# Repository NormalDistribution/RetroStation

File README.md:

A retro handheld gamestation based on the Raspberry Pi.

Be sure to check out our product status page:
https://github.com/NormalDistribution/RetroStation/wiki

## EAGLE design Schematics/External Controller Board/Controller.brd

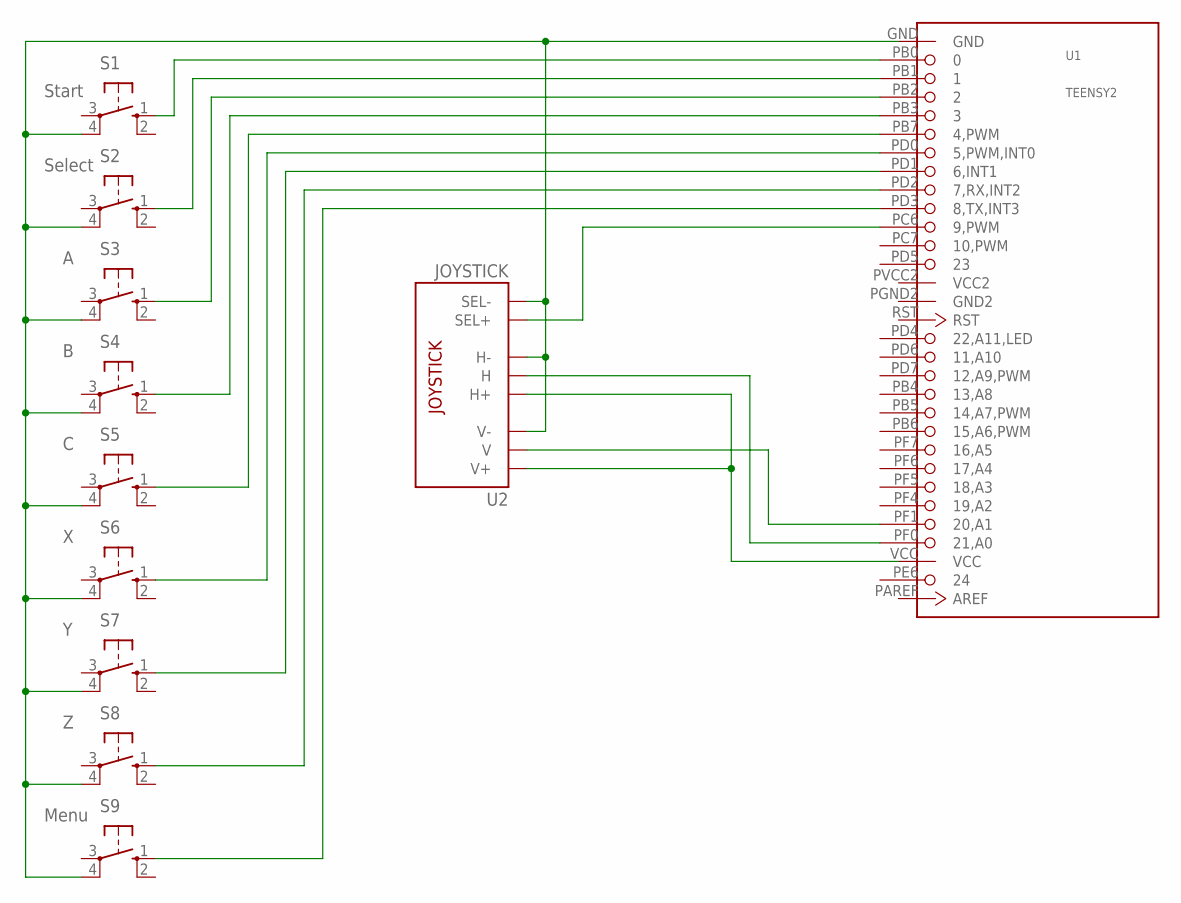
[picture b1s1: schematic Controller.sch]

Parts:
S1, S2, S3, S4, S5, S6, S7, S8, S9: 10-XX; B3F-10XX
U1: TEENSY2
U2: JOYSTICK

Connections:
GND2: U1.PGND2 (GND2)
unnamed: S1.1 (S), U1.PB0 (0)
unnamed: S2.1 (S), U1.PB1 (1)
unnamed: S3.1 (S), U1.PB2 (2)
unnamed: S4.1 (S), U1.PB3 (3)
unnamed: S5.1 (S), U1.PB7 (4,PWM)
unnamed: S6.1 (S), U1.PD0 (5,PWM,INT0)
unnamed: S7.1 (S), U1.PD1 (6,INT1)
unnamed: S8.1 (S), U1.PD2 (7,RX,INT2)
unnamed: U1.PC6 (9,PWM), U2.B1A (SEL+)
unnamed: U1.VCC, U2.H1 (H+), U2.V1 (V+)
unnamed: U1.PF0 (21,A0), U2.H2 (H)
unnamed: S9.1 (S), U1.PD3 (8,TX,INT3)
unnamed: S1.4 (P1), S2.4 (P1), S3.4 (P1), S4.4 (P1), S5.4 (P1), S6.4 (P1), S7.4 (P1), S8.4 (P1), S9.4 (P1), U1.GND, U2.B2A (SEL-), U2.H3 (H-), U2.V3 (V-)
unnamed: U1.PF1 (20,A1), U2.V2 (V)
VCC2: U1.PVCC2 (VCC2)

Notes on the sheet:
Start
Select
Menu

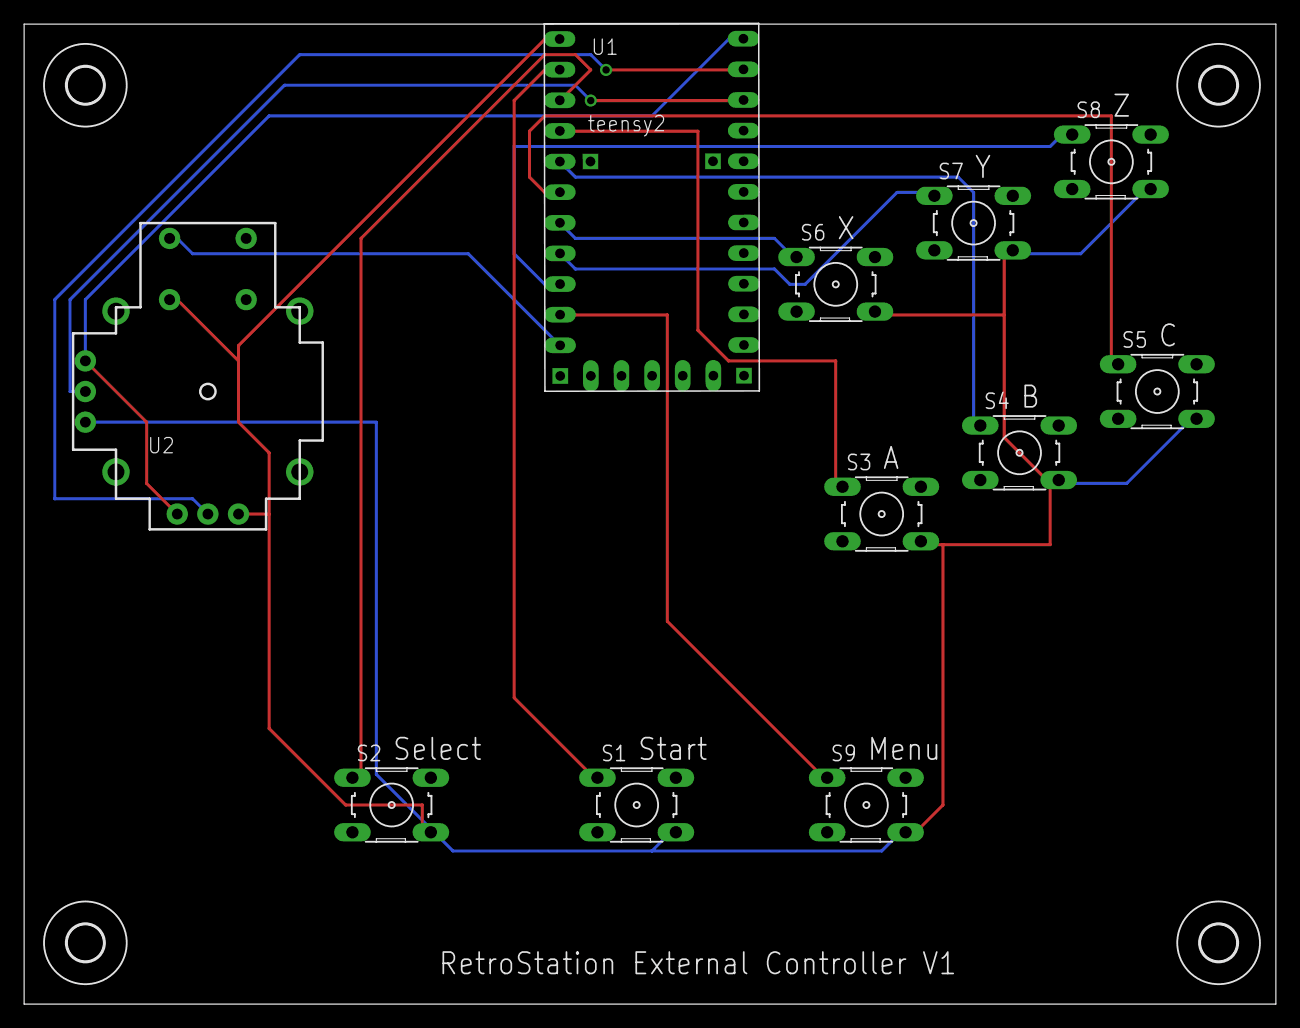
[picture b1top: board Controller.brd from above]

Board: 2 copper layers, 103.8 x 81.3 mm, 15 parts (0 on the bottom side), 14 nets.

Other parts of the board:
U$1, U$2, U$3, U$4: 3,0

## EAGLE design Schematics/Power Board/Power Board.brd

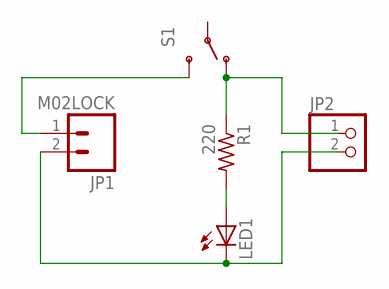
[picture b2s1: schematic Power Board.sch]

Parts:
JP1: M02LOCK; 1X02_LOCK
JP2: PINHD-1X2; 1X02
LED1: LED3MM
R1: 220; 0204/5
S1: SWITCH-SPDTPTH; SWITCH-SPDT

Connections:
unnamed: JP2.1, R1.1, S1.1 (O)
unnamed: JP1.1, S1.3 (S)
unnamed: LED1.A, R1.2
unnamed: JP1.2, JP2.2, LED1.K (C)

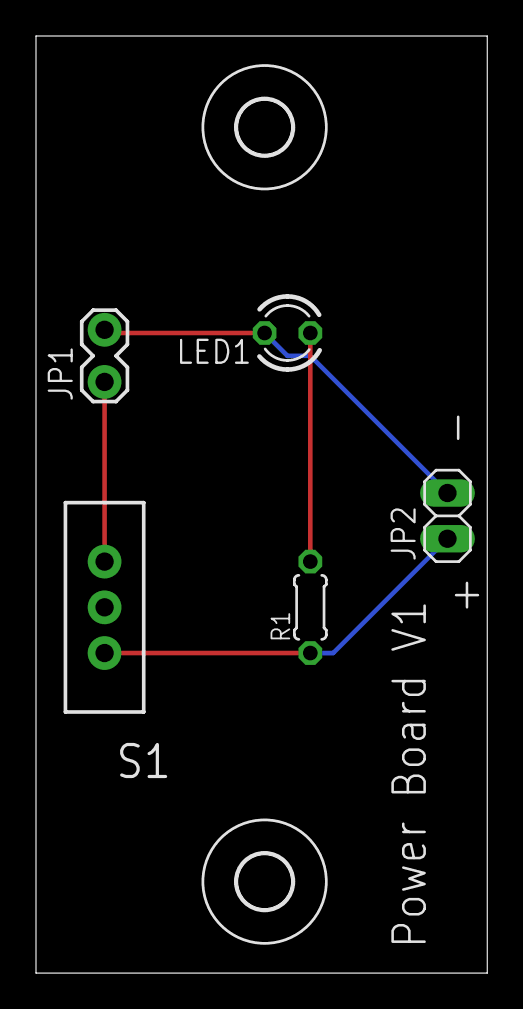
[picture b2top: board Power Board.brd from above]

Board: 2 copper layers, 25.1 x 52.1 mm, 7 parts (0 on the bottom side), 4 nets.

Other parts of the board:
U$1, U$2: 3,0

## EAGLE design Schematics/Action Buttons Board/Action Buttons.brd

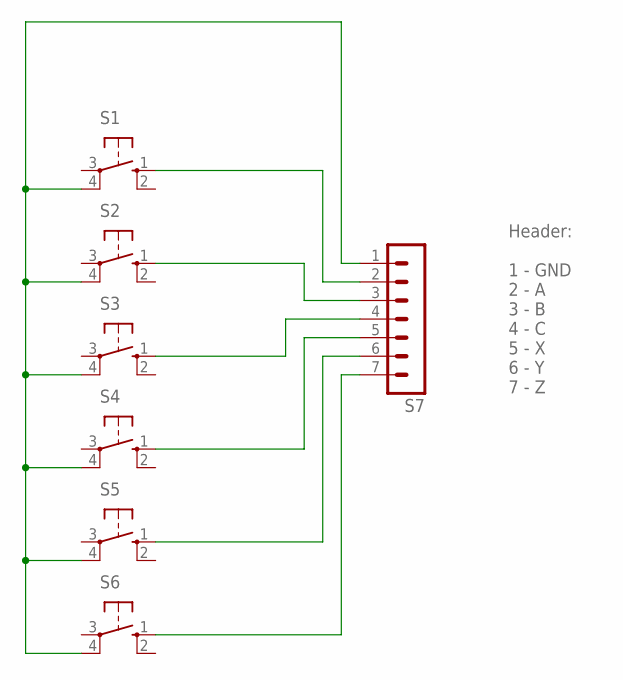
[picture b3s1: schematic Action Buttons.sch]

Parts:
S1, S2, S3, S4, S5, S6: 10-XX; B3F-10XX
S7: MA07-1

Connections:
unnamed: S1.4 (P1), S2.4 (P1), S3.4 (P1), S4.4 (P1), S5.4 (P1), S6.4 (P1), S7.1
unnamed: S1.1 (S), S7.2
unnamed: S2.1 (S), S7.3
unnamed: S3.1 (S), S7.4
unnamed: S4.1 (S), S7.5
unnamed: S5.1 (S), S7.6
unnamed: S6.1 (S), S7.7

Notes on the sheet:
Header: 1 - GND 2 - A 3 - B 4 - C 5 - X 6 - Y 7 - Z

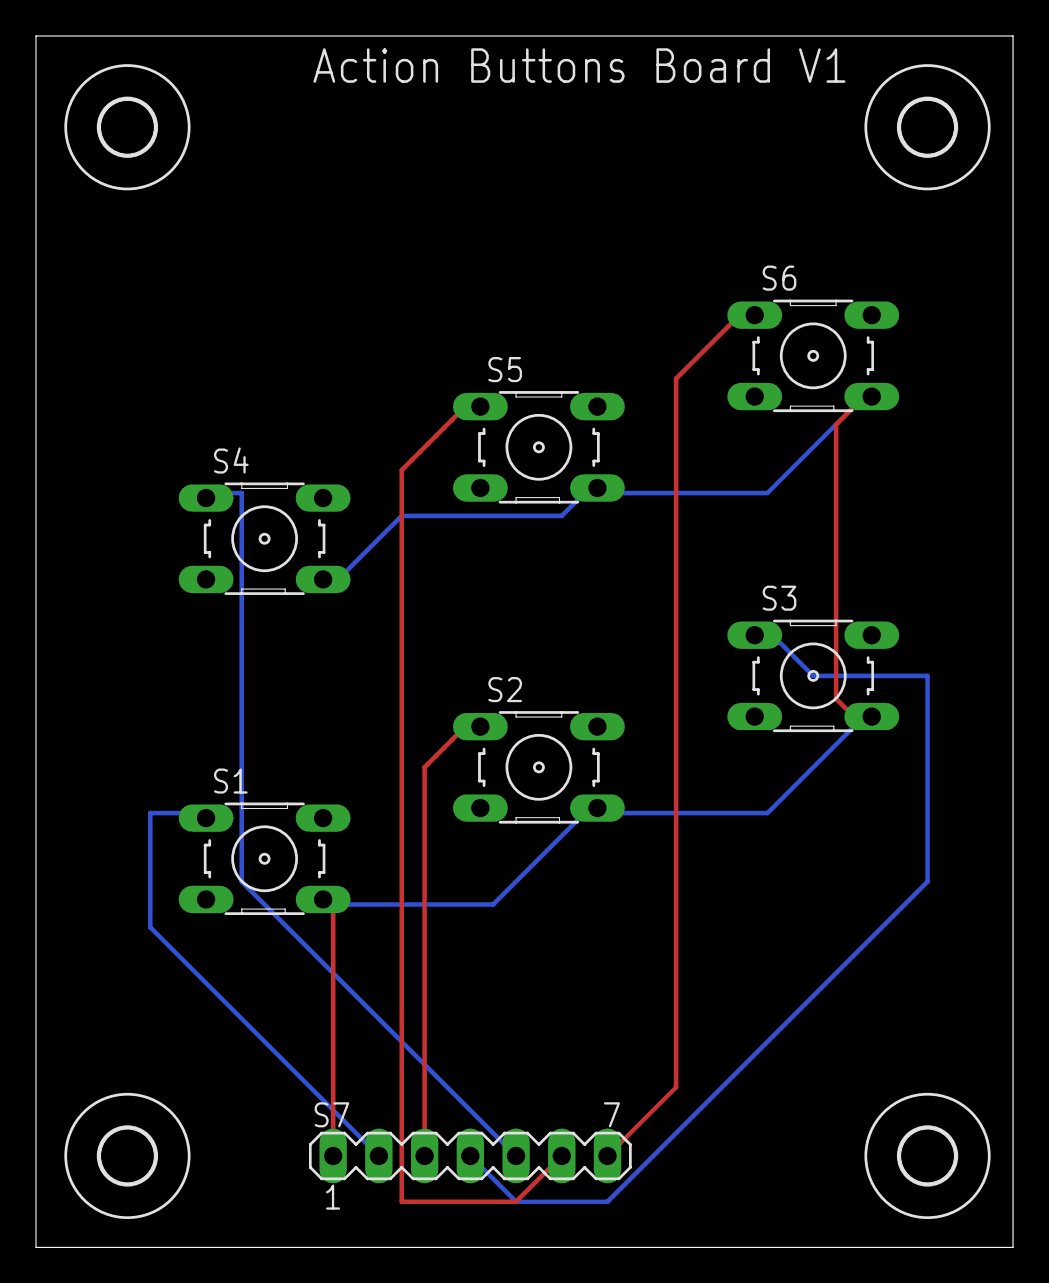
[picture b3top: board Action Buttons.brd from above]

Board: 2 copper layers, 54.3 x 67.3 mm, 11 parts (0 on the bottom side), 7 nets.

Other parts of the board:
U$1, U$2, U$3, U$4: 3,0

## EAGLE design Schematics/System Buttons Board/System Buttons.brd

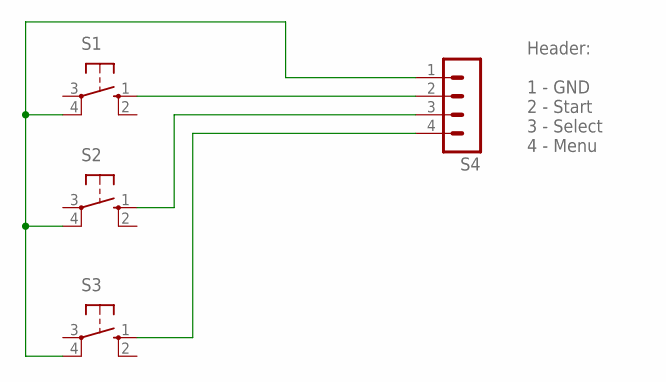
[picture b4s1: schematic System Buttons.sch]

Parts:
S1, S2, S3: 10-XX; B3F-10XX
S4: MA04-1

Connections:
unnamed: S1.4 (P1), S2.4 (P1), S3.4 (P1), S4.1
unnamed: S1.1 (S), S4.2
unnamed: S2.1 (S), S4.3
unnamed: S3.1 (S), S4.4

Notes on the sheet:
Header: 1 - GND 2 - Start 3 - Select 4 - Menu

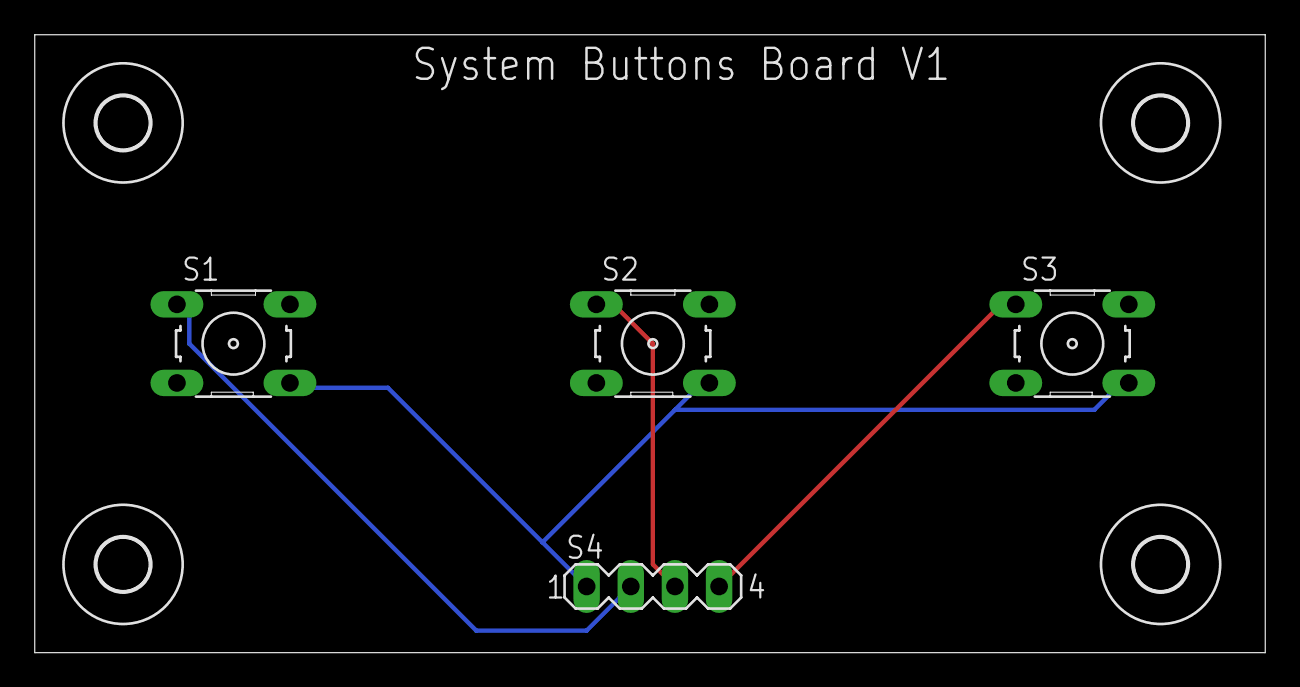
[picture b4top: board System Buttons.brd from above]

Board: 2 copper layers, 70.8 x 35.5 mm, 8 parts (0 on the bottom side), 4 nets.

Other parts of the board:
U$1, U$2, U$3, U$4: 3,0

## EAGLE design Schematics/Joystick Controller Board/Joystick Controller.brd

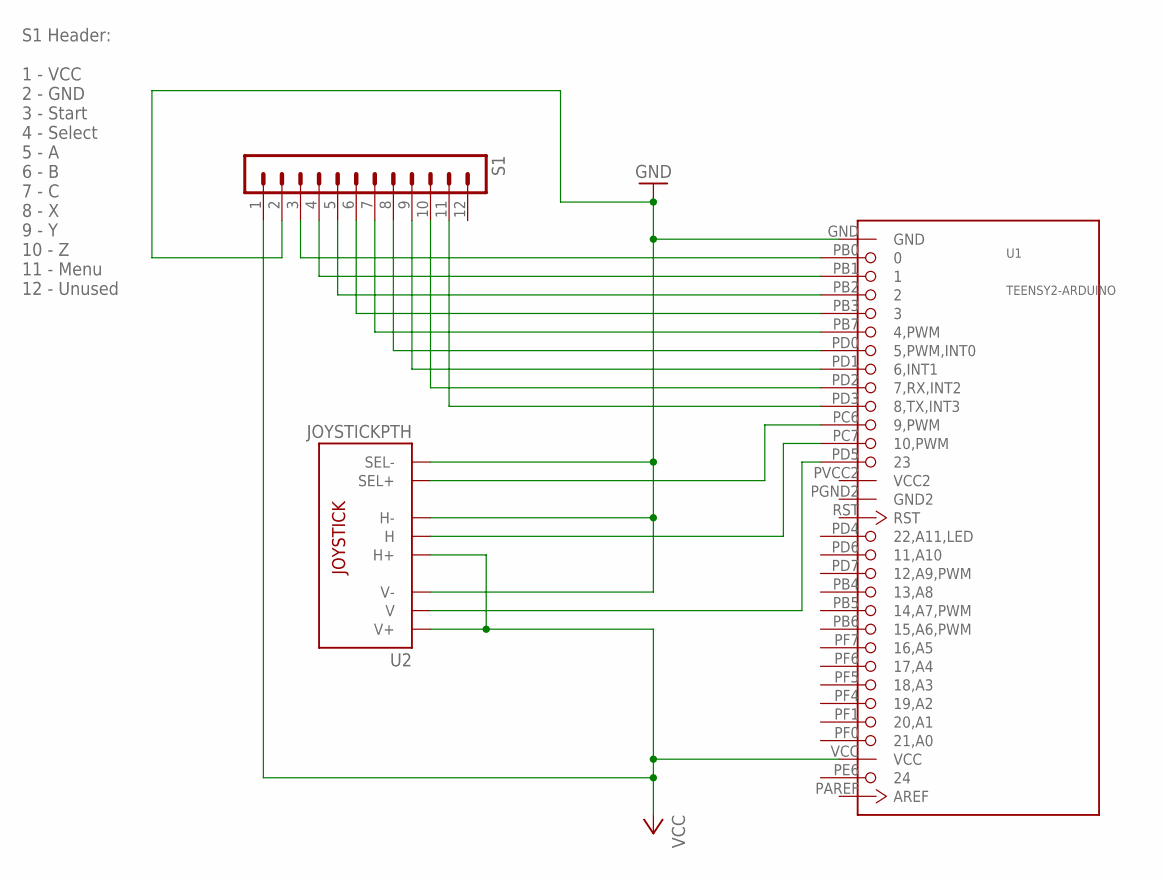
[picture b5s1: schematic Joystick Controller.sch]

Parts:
S1: MA12-1
U1: TEENSY2-ARDUINO; TEENSY2
U2: JOYSTICKPTH; JOYSTICK

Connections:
GND: S1.2, U1.GND, U2.B2A (SEL-), U2.H3 (H-), U2.V3 (V-)
GND2: U1.PGND2 (GND2)
unnamed: U1.PC6 (9,PWM), U2.B1A (SEL+)
unnamed: U1.PC7 (10,PWM), U2.H2 (H)
unnamed: U1.PD5 (23), U2.V2 (V)
unnamed: S1.3, U1.PB0 (0)
unnamed: S1.4, U1.PB1 (1)
unnamed: S1.5, U1.PB2 (2)
unnamed: S1.6, U1.PB3 (3)
unnamed: S1.7, U1.PB7 (4,PWM)
unnamed: S1.8, U1.PD0 (5,PWM,INT0)
unnamed: S1.9, U1.PD1 (6,INT1)
unnamed: S1.10, U1.PD2 (7,RX,INT2)
unnamed: S1.11, U1.PD3 (8,TX,INT3)
VCC: S1.1, U1.VCC, U2.H1 (H+), U2.V1 (V+)
VCC2: U1.PVCC2 (VCC2)

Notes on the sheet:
S1 Header: 1 - VCC 2 - GND 3 - Start 4 - Select 5 - A 6 - B 7 - C 8 - X 9 - Y 10 - Z 11 - Menu 12 - Unused

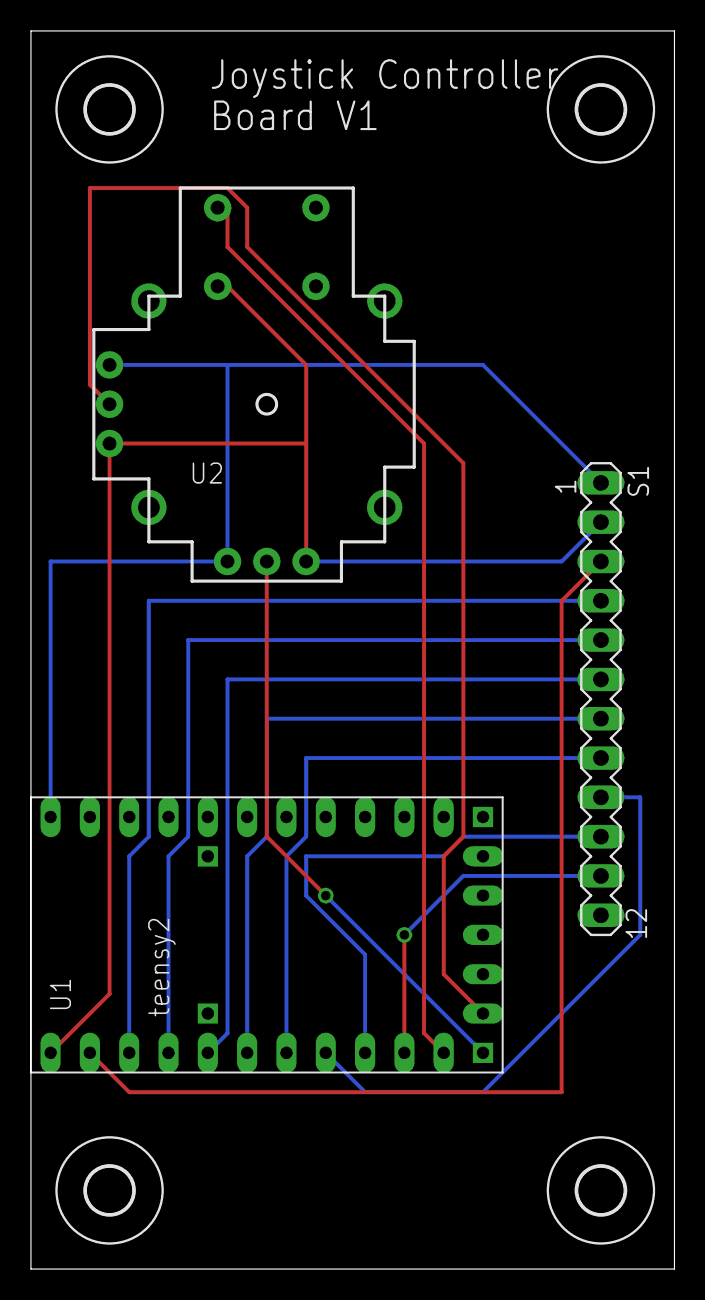
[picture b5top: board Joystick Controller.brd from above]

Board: 2 copper layers, 41.6 x 80.0 mm, 7 parts (0 on the bottom side), 14 nets.

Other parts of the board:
U$1, U$2, U$3, U$4: 3,0

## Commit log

2014-01-02 First code commit.
2014-01-03 Directory structure created Spalsh screen created.
2014-01-03 Controller board schematic started
2014-01-03 Mockup Created
2014-01-07 Schematics updated to reflect the use of the internal pull-up resistors of the controller's microcontroller Firmware for the internal controller's microcontroller started
2014-01-07 Created seperate circuits for each button panel.
2014-01-07 Added images for each schematic and PCB
2014-01-07 Added power board schematic
2014-01-08 Initial power board schematic complete.
2014-01-08 External controller board updated.
2014-01-08 Schematics updated External Controller board schematic created
2014-01-11 Updated the schematics for the external controller.
2014-01-13 External controller firmware created.
2014-01-14 Added the files to start developing the main menu and RetroManager.
2014-01-14 Update python menu script
2014-01-15 Code has been started for the web ROM manager (RetroManager)
2014-01-16 More work done to the RetroManager web app.
2014-07-11 Boot menu code started.
2014-07-11 Updated boot menu code.
2014-07-12 Updated the menu system a bit
2014-07-15 General modifications to the menu system.

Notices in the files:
parts and their libraries:
SparkFun-Electromechanical: Licensing: CC v3.0 Share-Alike You are welcome to use this library for commercial purposes.
